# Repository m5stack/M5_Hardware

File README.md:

# M5Stack Hardware Repository

[中文](README_CN.md) | English

Welcome to the M5Stack open-source hardware repository! This repository contains hardware design files for M5Stack product series, including PCB designs, structural files, and KiCad libraries.

## 📁 Directory Structure

```
M5_Hardware/
├── Common/              # Common module designs (Atomic, Module, Unit types)
├── Products/            # Product designs organized by SKU
│   ├── [SKU_Name]/
│   │   ├── Footprints/        # PCB design files
│   │   └── Structures/ # 2D/3D structure files
│   └── ...
├── KiCad/              # KiCad library files
│   ├── 3D/             # 3D models
│   ├── Footprints/     # Footprint library
│   └── Symbols/        # Symbol library
└── Docs/               # Documentation
```

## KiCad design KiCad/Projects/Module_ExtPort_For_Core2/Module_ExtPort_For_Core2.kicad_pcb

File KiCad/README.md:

# M5Stack KiCad Library

**The libraries in this repository are intended to be used with KiCad version 7.**

Each footprint library is stored as a directory with the .pretty suffix. The footprint files are .kicad_mod files within. And 3D model files are stored in the ``3D/M5Stack.3dshapes/`` folder.

### Contributing

If you want to contribute, please consider sending us a Pull Request (PR).

### 3D Models

We provide some 3D models to help you with your project inside the ``3D/M5Stack.3dshapes/`` folder.

To use the files, you need to create an environment variable pointing to this ``KiCad`` folder path.

* Open ``Preferences`` -> ``Configure Paths...``
* Create the new variable:
    * Name: ``KICAD_M5STACK``
    * Path: ``/path/to/this/KiCad``
* Then 3D models can be referenced as: ``${KICAD_M5STACK}/3D/M5Stack.3dshapes/model_name.step``

### About KiCad

KiCad is a Cross-Platform and Open Source Electronics Design Automation Suite. See [KiCad EDA](https://kicad.org/) for more information.

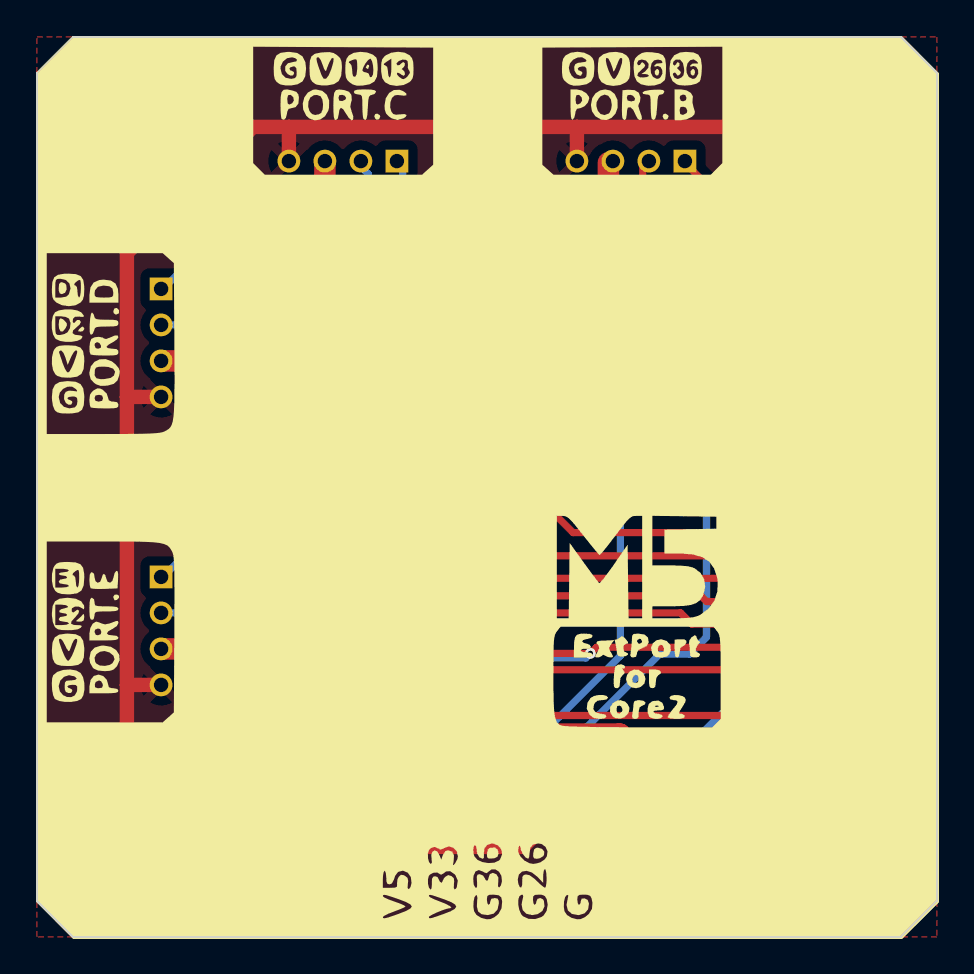
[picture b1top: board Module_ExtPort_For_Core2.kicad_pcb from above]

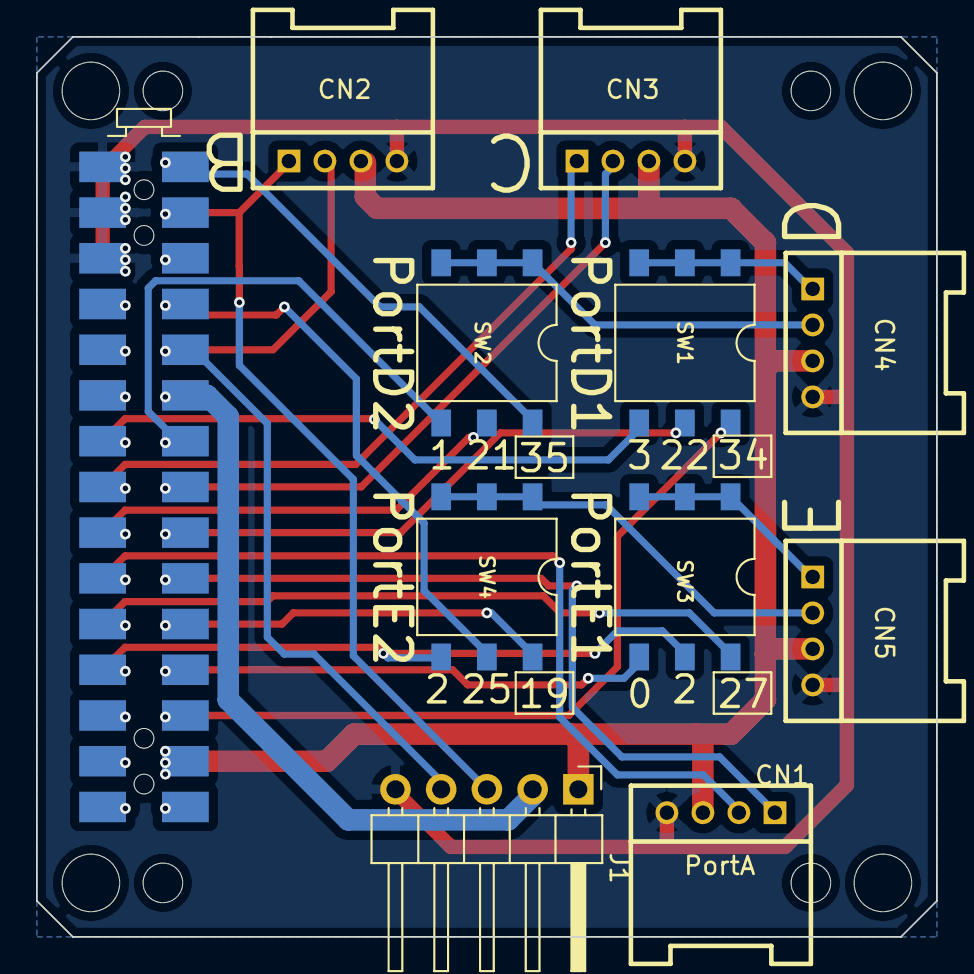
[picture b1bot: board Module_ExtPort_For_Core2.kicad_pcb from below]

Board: 2 copper layers, 50.0 x 50.0 mm, 11 parts (10 on the bottom side), 24 nets.

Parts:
CN1, CN2, CN3, CN4, CN5: CON_GROVE; CON_GROVE_H
CN6: CON_MBUS_bottom_Core2; M5STACK_BUS_30P
J1: Conn_01x05; PinHeader_1x05_P2.54mm_Horizontal
SW1, SW2, SW3, SW4: SW_DIP_x03; SMDIP-6_W9.53mm_narrow

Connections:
+3V3: CN6.12 (3V3), J1.2
+5V: CN1.3, CN2.3, CN3.3, CN4.3, CN5.3, CN6.28 (5V), J1.1
/EXT_G0: CN6.24 (G0-I2C_LRCK-PDM_CLK), SW3.4
/EXT_G1: CN6.14 (G1-TXD0), SW2.4
/EXT_G2: CN6.23 (G2_I2C_DOUT), SW3.5, SW4.4
/EXT_G3: CN6.13 (G3-RXD0), SW1.4
/EXT_G13: CN3.1, CN6.15 (G13-RXD2)
/EXT_G14: CN3.2, CN6.16 (G14-TXD2)
/EXT_G19: CN6.22 (G19), SW4.6
/EXT_G21: CN6.17 (G21-intSDA), SW2.5
/EXT_G22: CN6.18 (G22-intSCL), SW1.5
/EXT_G25: CN6.8 (G25-DAC), SW4.5
/EXT_G26: CN2.2, CN6.10 (G26-DAC), J1.4
/EXT_G27: CN6.21 (G27), SW3.6
/EXT_G32: CN1.2, CN6.19 (G32_PA_SDA)
/EXT_G33: CN1.1, CN6.20 (G33_PA_SCL)
/EXT_G34: CN6.26 (G34-PDM_DAT), SW1.6
/EXT_G35: CN6.2 (G35-ADC), SW2.6
/EXT_G36: CN2.1, CN6.4 (G36-ADC), J1.3
/PD1: CN4.1, SW1.1, SW1.2, SW1.3
/PD2: CN4.2, SW2.1, SW2.2, SW2.3
/PE1: CN5.1, SW3.1, SW3.2, SW3.3
/PE2: CN5.2, SW4.1, SW4.2, SW4.3
GND: CN1.4, CN2.4, CN3.4, CN4.4, CN5.4, CN6.1 (GND), CN6.3 (GND1), CN6.5 (GND2), J1.5

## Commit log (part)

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2021-11-04 init
2021-11-04 add bus module pcb
2022-03-22 update some product size
2022-03-31 update module-type file
2022-04-15 add DMX sch
2022-06-29 add ExtPortForCore2
2022-10-21 update Module Type A dimensions
2023-02-12 Add STAMP series kicad footprint
2023-02-12 Create LICENSE
2023-02-16 M5KiCad: update STAMPS3 3D model
2023-02-24 Update README.md
    STAMP-S3 footprints seem to require KICAD 7 or later.
2023-07-13 Add STAMPS3 Kicad symbol
    Add Kicad symbol
2023-12-07 Add M5StampS3 1.27mm socket footprint
2024-08-22 add Stamp-Fly-Battery-Protect-Component
2024-10-05 add AtomS3R Proto
2024-10-16 add M5Atomic 3D file
2025-04-22 Add M5StampS3 2.54mm socket footprint
    Based on M5StampS3 1.27mm footprint, this footprint has
    - unused pins removed
    - 3D model of pins removed as pins incorrect pitch
    - through holes enlarged to 1mm with 1.7mm pads
2025-08-31 Fix error
2026-01-24 update repo format and release some product 3d file
2026-01-24 add KiCad / Project Module_ExtPort_For_Core2
2026-02-04 add Module_Type_A_CoreS3_M5_Bus.PcbDoc
2026-03-09 add Stamp C6LoRa and update folder format
2026-03-11 add Stamp C6LoRa kicad mod
2026-03-13 update Stamp C6LoRa STEP
2026-03-19 Fix Cardputer-Adv Bottom file and add Stamp-S3Bat PcbDoc
2026-03-26 add structures file of S013
2026-04-10 add stamp-C3
2026-05-25 add stackchan structures
2026-06-22 add C148, C145 and C152
2026-06-23 Add five structures
2026-06-23 Add K127 structure
2026-06-23 add K135
2026-06-24 add K006-V27, K010-AWS,K007-V27,K034,K150 structures
2026-06-25 added C008-C,C008,C126-ECHO,C008-B and C008-B-V11 structures
2026-06-26 added structures of C123,C124,C126,C126-CAM and K125
2026-06-29 added structures of C126-Ext,C126-M12,D062-M12,K147 and K147-CAM
2026-06-30 added structures of S015,K129-V11,K132-V11 and S015-DIP
